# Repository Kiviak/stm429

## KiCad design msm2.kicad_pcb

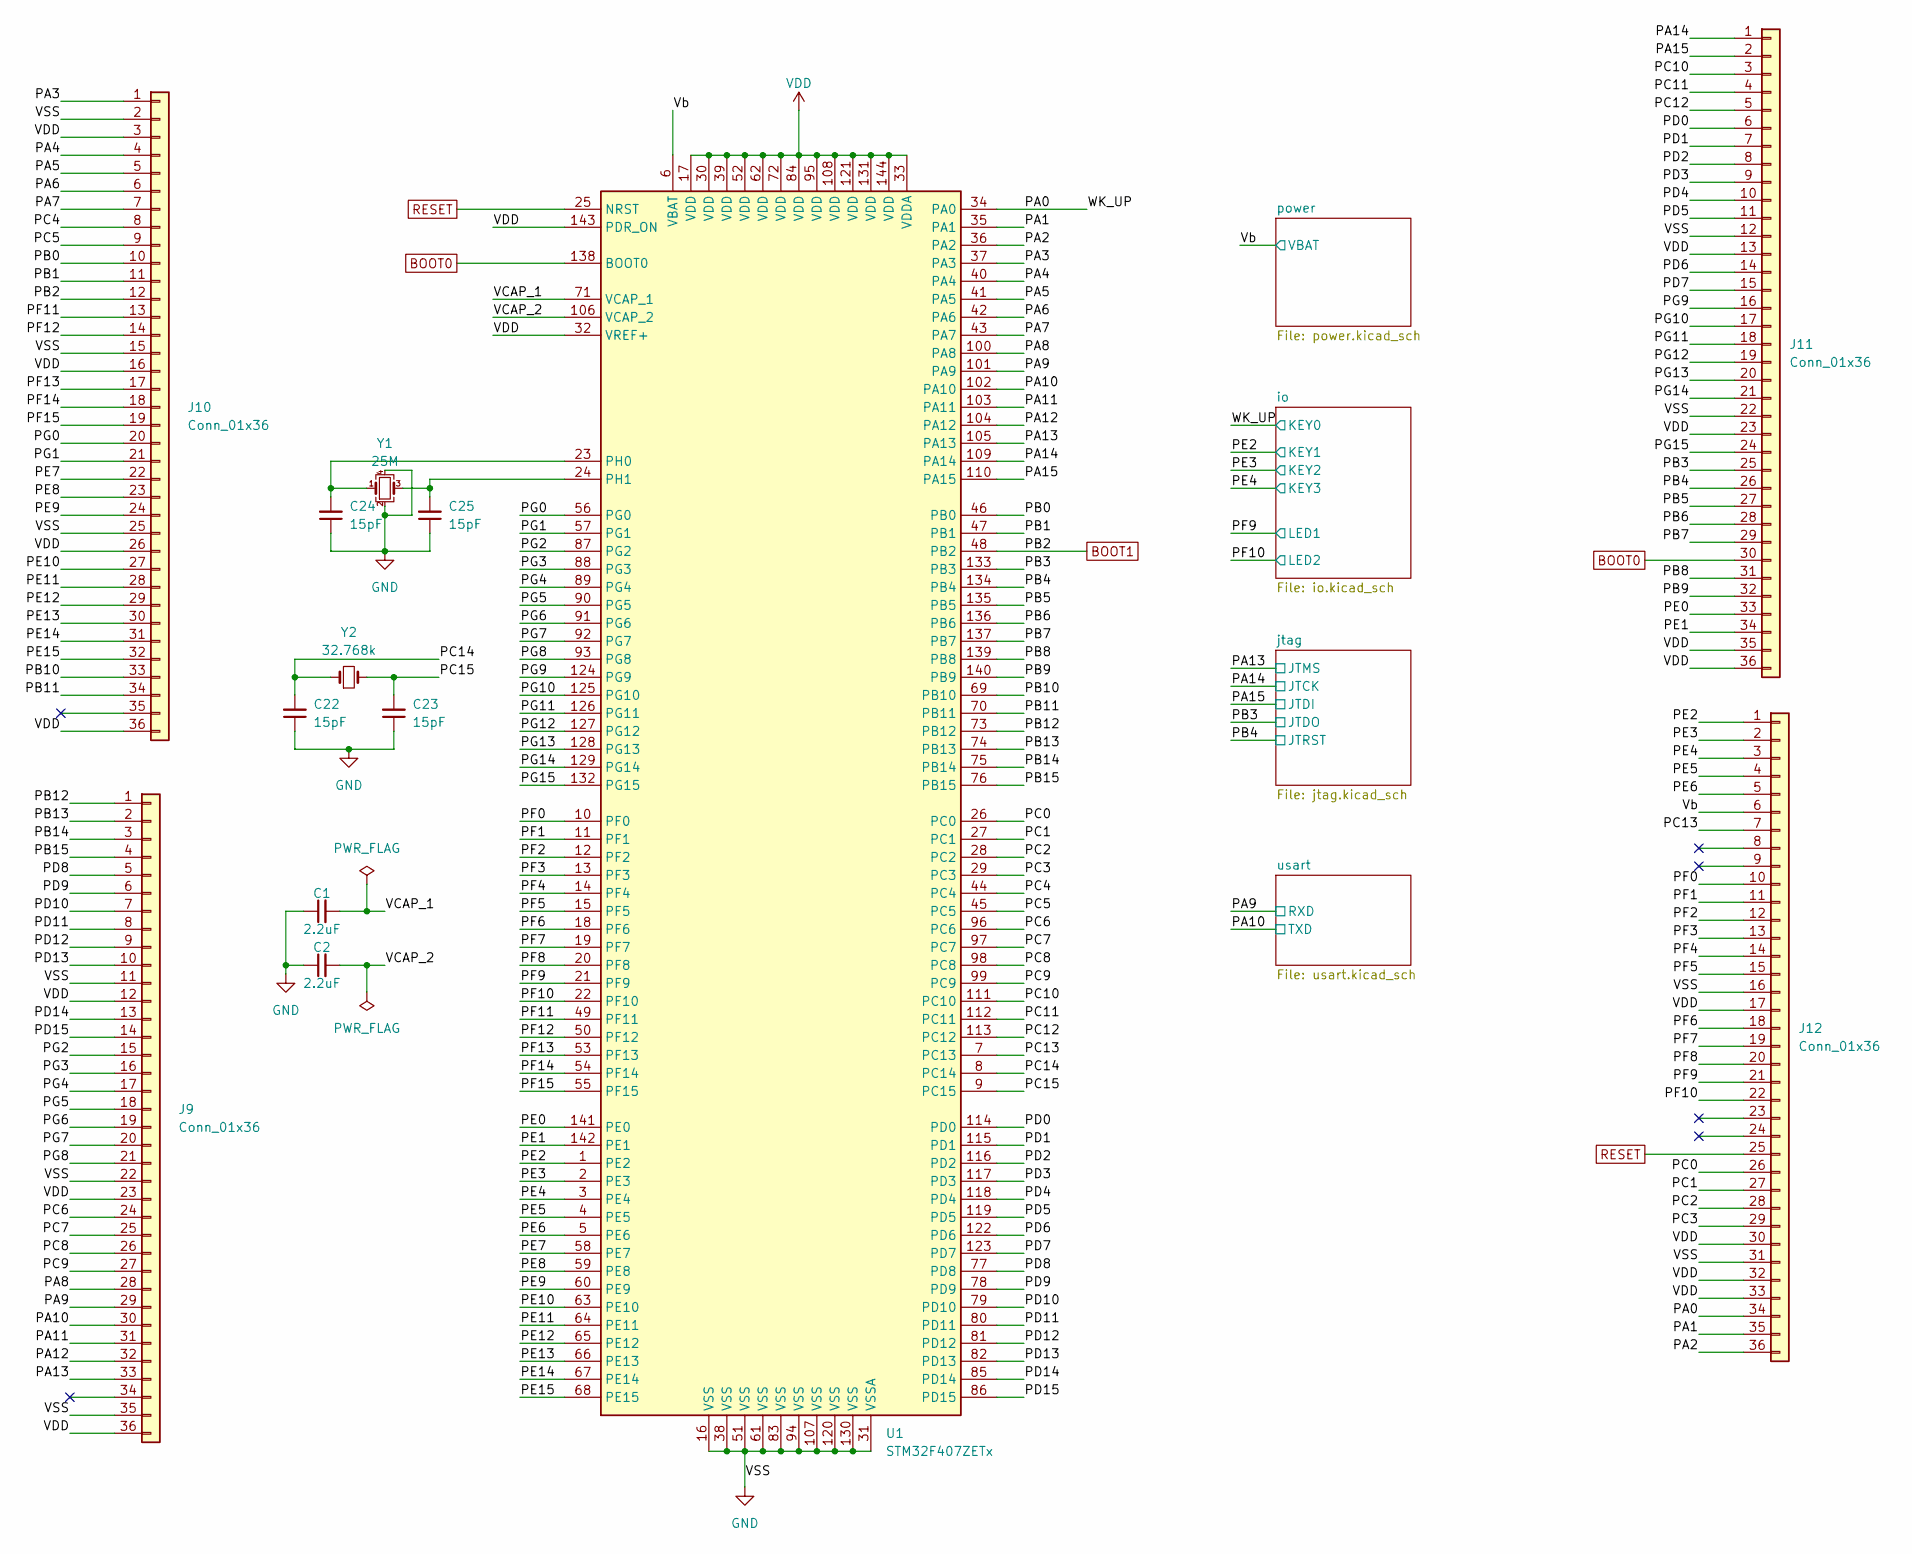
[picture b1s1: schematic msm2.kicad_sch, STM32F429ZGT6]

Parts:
C1, C2: 2.2uF; C_0603_1608Metric_Pad1.08x0.95mm_HandSolder
C22, C23, C24, C25: 15pF; C_0603_1608Metric_Pad1.08x0.95mm_HandSolder
J9, J10, J11, J12: Conn_01x36; PinHeader_1x36_P2.54mm_Vertical
U1: STM32F407ZETx; LQFP-144_20x20mm_P0.5mm
Y1: 25M; Crystal_SMD_3225-4Pin_3.2x2.5mm_HandSoldering
Y2: 32.768k; Crystal_SMD_3215-2Pin_3.2x1.5mm

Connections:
/PA0: J12.34, U1.34 (PA0); also elsewhere on the board
/PA1: J12.35, U1.35 (PA1)
/PA2: J12.36, U1.36 (PA2)
/PA3: J10.1, U1.37 (PA3)
/PA4: J10.4, U1.40 (PA4)
/PA5: J10.5, U1.41 (PA5)
/PA6: J10.6, U1.42 (PA6)
/PA7: J10.7, U1.43 (PA7)
/PA8: J9.28, U1.100 (PA8)
/PA9: J9.29, U1.101 (PA9); also elsewhere on the board
/PA10: J9.30, U1.102 (PA10); also elsewhere on the board
/PA11: J9.31, U1.103 (PA11)
/PA12: J9.32, U1.104 (PA12)
/PA13: J9.33, U1.105 (PA13); also elsewhere on the board
/PA14: J11.1, U1.109 (PA14); also elsewhere on the board
/PA15: J11.2, U1.110 (PA15); also elsewhere on the board
/PB0: J10.10, U1.46 (PB0)
/PB1: J10.11, U1.47 (PB1)
/PB3: J11.25, U1.133 (PB3); also elsewhere on the board
/PB4: J11.26, U1.134 (PB4); also elsewhere on the board
/PB5: J11.27, U1.135 (PB5)
/PB6: J11.28, U1.136 (PB6)
/PB7: J11.29, U1.137 (PB7)
/PB8: J11.31, U1.139 (PB8)
/PB9: J11.32, U1.140 (PB9)
/PB10: J10.33, U1.69 (PB10)
/PB11: J10.34, U1.70 (PB11)
/PB12: J9.1, U1.73 (PB12)
/PB13: J9.2, U1.74 (PB13)
/PB14: J9.3, U1.75 (PB14)
/PB15: J9.4, U1.76 (PB15)
/PC0: J12.26, U1.26 (PC0)
/PC1: J12.27, U1.27 (PC1)
/PC2: J12.28, U1.28 (PC2)
/PC3: J12.29, U1.29 (PC3)
/PC4: J10.8, U1.44 (PC4)
/PC5: J10.9, U1.45 (PC5)
/PC6: J9.24, U1.96 (PC6)
/PC7: J9.25, U1.97 (PC7)
/PC8: J9.26, U1.98 (PC8)
/PC9: J9.27, U1.99 (PC9)
/PC10: J11.3, U1.111 (PC10)
/PC11: J11.4, U1.112 (PC11)
/PC12: J11.5, U1.113 (PC12)
/PC13: J12.7, U1.7 (PC13)
/PC14: C22.2, U1.8 (PC14), Y2.1
/PC15: C23.2, U1.9 (PC15), Y2.2
/PD0: J11.6, U1.114 (PD0)
/PD1: J11.7, U1.115 (PD1)
/PD2: J11.8, U1.116 (PD2)
/PD3: J11.9, U1.117 (PD3)
/PD4: J11.10, U1.118 (PD4)
/PD5: J11.11, U1.119 (PD5)
/PD6: J11.14, U1.122 (PD6)
/PD7: J11.15, U1.123 (PD7)
/PD8: J9.5, U1.77 (PD8)
/PD9: J9.6, U1.78 (PD9)
/PD10: J9.7, U1.79 (PD10)
/PD11: J9.8, U1.80 (PD11)
/PD12: J9.9, U1.81 (PD12)
/PD13: J9.10, U1.82 (PD13)
/PD14: J9.13, U1.85 (PD14)
/PD15: J9.14, U1.86 (PD15)
/PE0: J11.33, U1.141 (PE0)
/PE1: J11.34, U1.142 (PE1)
/PE2: J12.1, U1.1 (PE2); also elsewhere on the board
/PE3: J12.2, U1.2 (PE3); also elsewhere on the board
/PE4: J12.3, U1.3 (PE4); also elsewhere on the board
/PE5: J12.4, U1.4 (PE5)
/PE6: J12.5, U1.5 (PE6)
/PE7: J10.22, U1.58 (PE7)
/PE8: J10.23, U1.59 (PE8)
/PE9: J10.24, U1.60 (PE9)
/PE10: J10.27, U1.63 (PE10)
/PE11: J10.28, U1.64 (PE11)
/PE12: J10.29, U1.65 (PE12)
/PE13: J10.30, U1.66 (PE13)
/PE14: J10.31, U1.67 (PE14)
/PE15: J10.32, U1.68 (PE15)
/PF0: J12.10, U1.10 (PF0)
/PF1: J12.11, U1.11 (PF1)
/PF2: J12.12, U1.12 (PF2)
/PF3: J12.13, U1.13 (PF3)
/PF4: J12.14, U1.14 (PF4)
/PF5: J12.15, U1.15 (PF5)
/PF6: J12.18, U1.18 (PF6)
/PF7: J12.19, U1.19 (PF7)
/PF8: J12.20, U1.20 (PF8)
/PF9: J12.21, U1.21 (PF9); also elsewhere on the board
/PF10: J12.22, U1.22 (PF10); also elsewhere on the board
/PF11: J10.13, U1.49 (PF11)
/PF12: J10.14, U1.50 (PF12)
/PF13: J10.17, U1.53 (PF13)
/PF14: J10.18, U1.54 (PF14)
/PF15: J10.19, U1.55 (PF15)
/PG0: J10.20, U1.56 (PG0)
/PG1: J10.21, U1.57 (PG1)
/PG2: J9.15, U1.87 (PG2)
/PG3: J9.16, U1.88 (PG3)
/PG4: J9.17, U1.89 (PG4)
/PG5: J9.18, U1.90 (PG5)
/PG6: J9.19, U1.91 (PG6)
/PG7: J9.20, U1.92 (PG7)
/PG8: J9.21, U1.93 (PG8)
/PG9: J11.16, U1.124 (PG9)
/PG10: J11.17, U1.125 (PG10)
/PG11: J11.18, U1.126 (PG11)
/PG12: J11.19, U1.127 (PG12)
/PG13: J11.20, U1.128 (PG13)
/PG14: J11.21, U1.129 (PG14)
/PG15: J11.24, U1.132 (PG15)
/VCAP_1: C1.2, U1.71 (VCAP_1)
/VCAP_2: C2.2, U1.106 (VCAP_2)
/Vb: J12.6, U1.6 (VBAT); also elsewhere on the board
BOOT0: J11.30, U1.138 (BOOT0); also elsewhere on the board
BOOT1: J10.12, U1.48 (PB2); also elsewhere on the board
GND: C1.1, C2.1, C22.1, C23.1, C24.1, C25.1, J9.11, J9.22, J9.35, J10.2, J10.15, J10.25, J11.12, J11.22, J12.16, J12.31, U1.16 (VSS), U1.31 (VSSA), U1.38 (VSS), U1.51 (VSS), U1.61 (VSS), U1.83 (VSS), U1.94 (VSS), U1.107 (VSS), U1.120 (VSS), U1.130 (VSS), Y1.2, Y1.4; also elsewhere on the board
unnamed: C24.2, U1.23 (PH0), Y1.1
unnamed: C25.2, U1.24 (PH1), Y1.3
RESET: J12.25, U1.25 (NRST); also elsewhere on the board
VDD: J9.12, J9.23, J9.36, J10.3, J10.16, J10.26, J10.36, J11.13, J11.23, J11.35, J11.36, J12.17, J12.30, J12.32, J12.33, U1.17 (VDD), U1.30 (VDD), U1.32 (VREF+), U1.33 (VDDA), U1.39 (VDD), U1.52 (VDD), U1.62 (VDD), U1.72 (VDD), U1.84 (VDD), U1.95 (VDD), U1.108 (VDD), U1.121 (VDD), U1.131 (VDD), U1.143 (PDR_ON), U1.144 (VDD); also elsewhere on the board

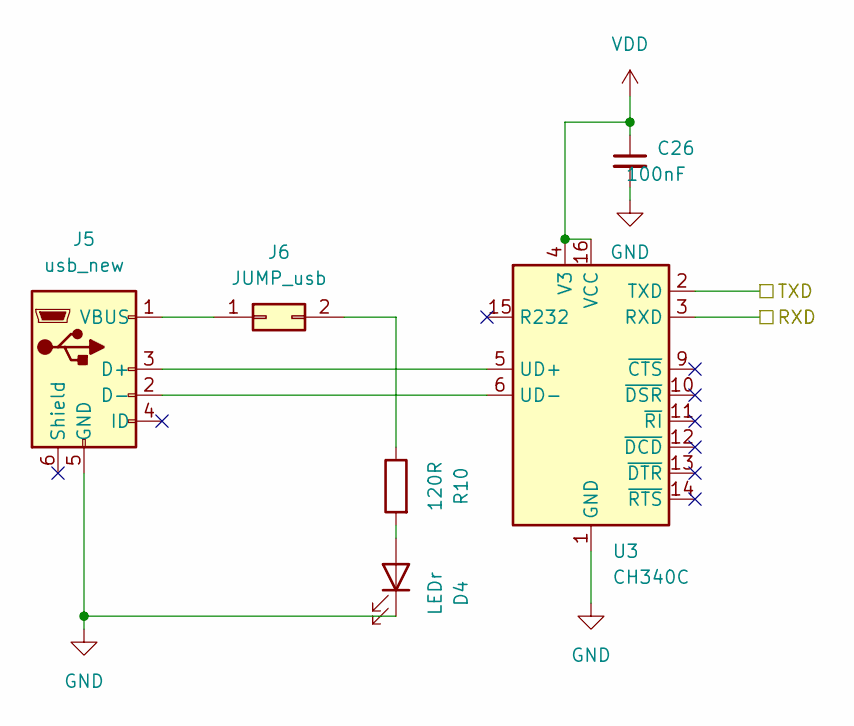
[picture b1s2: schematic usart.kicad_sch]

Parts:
C26: 100nF; C_0603_1608Metric_Pad1.08x0.95mm_HandSolder
D4: LEDr; LED_0603_1608Metric_Pad1.05x0.95mm_HandSolder
J5: usb_new; USB_Micro-B_GCT_USB3076-30-A
J6: JUMP_usb; PinHeader_2x01_P2.54mm_Vertical
R10: 120R; R_0603_1608Metric_Pad0.98x0.95mm_HandSolder
U3: CH340C; SOIC-16_3.9x9.9mm_P1.27mm

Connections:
/PA9: U3.3 (RXD); also elsewhere on the board
/PA10: U3.2 (TXD); also elsewhere on the board
GND: C26.2, D4.1 (K), J5.5 (GND), U3.1 (GND); also elsewhere on the board
unnamed: D4.2 (A), R10.2
unnamed: J5.1 (VBUS), J6.1
unnamed: J5.2 (D-), U3.6 (UD-)
unnamed: J5.3 (D+), U3.5 (UD+)
unnamed: J6.2, R10.1
VDD: C26.1, U3.4 (V3), U3.16 (VCC); also elsewhere on the board

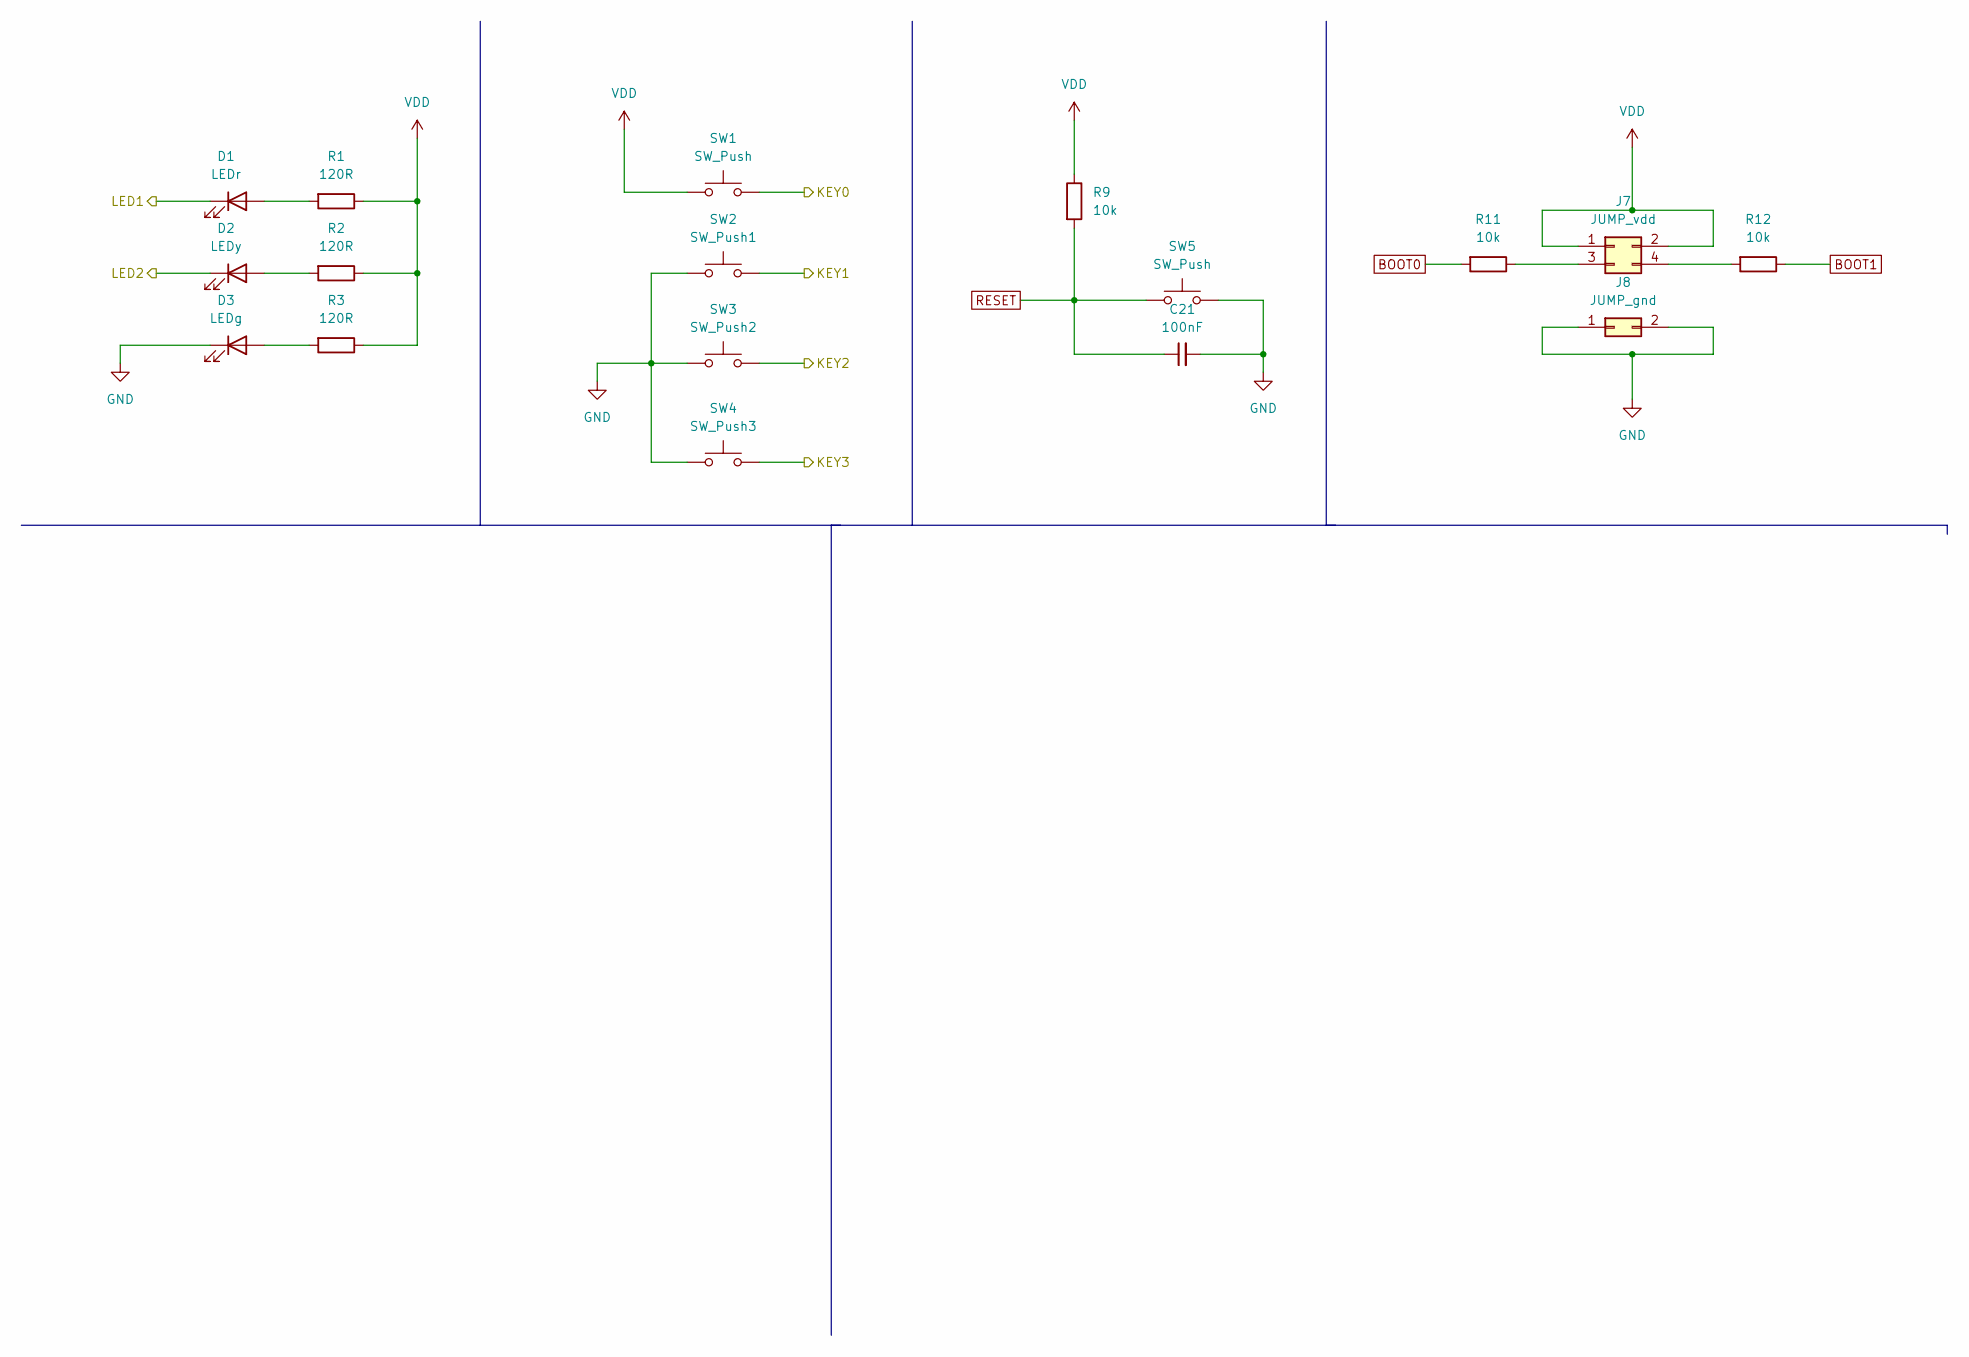
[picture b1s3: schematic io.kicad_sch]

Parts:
C21: 100nF; C_0603_1608Metric_Pad1.08x0.95mm_HandSolder
D1: LEDr; LED_0603_1608Metric_Pad1.05x0.95mm_HandSolder
D2: LEDy; LED_0603_1608Metric_Pad1.05x0.95mm_HandSolder
D3: LEDg; LED_0603_1608Metric_Pad1.05x0.95mm_HandSolder
J7: JUMP_vdd; PinHeader_2x02_P2.54mm_Vertical
J8: JUMP_gnd; PinHeader_2x01_P2.54mm_Vertical
R1, R2, R3: 120R; R_0603_1608Metric_Pad0.98x0.95mm_HandSolder
R9, R11, R12: 10k; R_0603_1608Metric_Pad0.98x0.95mm_HandSolder
SW1, SW5: SW_Push; SW_Push_6x3.6mm_H2.5mm
SW2: SW_Push1; SW_Push_6x3.6mm_H2.5mm
SW3: SW_Push2; SW_Push_6x3.6mm_H2.5mm
SW4: SW_Push3; SW_Push_6x3.6mm_H2.5mm

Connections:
/PA0: SW1.2; also elsewhere on the board
/PE2: SW2.2; also elsewhere on the board
/PE3: SW3.2; also elsewhere on the board
/PE4: SW4.2; also elsewhere on the board
/PF9: D1.1 (K); also elsewhere on the board
/PF10: D2.1 (K); also elsewhere on the board
BOOT0: R11.2; also elsewhere on the board
BOOT1: R12.1; also elsewhere on the board
GND: C21.2, D3.1 (K), J8.1, J8.2, SW2.1, SW3.1, SW4.1, SW5.2; also elsewhere on the board
unnamed: D1.2 (A), R1.2
unnamed: D2.2 (A), R2.2
unnamed: D3.2 (A), R3.2
unnamed: J7.3, R11.1
unnamed: J7.4, R12.2
RESET: C21.1, R9.2, SW5.1; also elsewhere on the board
VDD: J7.1, J7.2, R1.1, R2.1, R3.1, R9.1, SW1.1; also elsewhere on the board

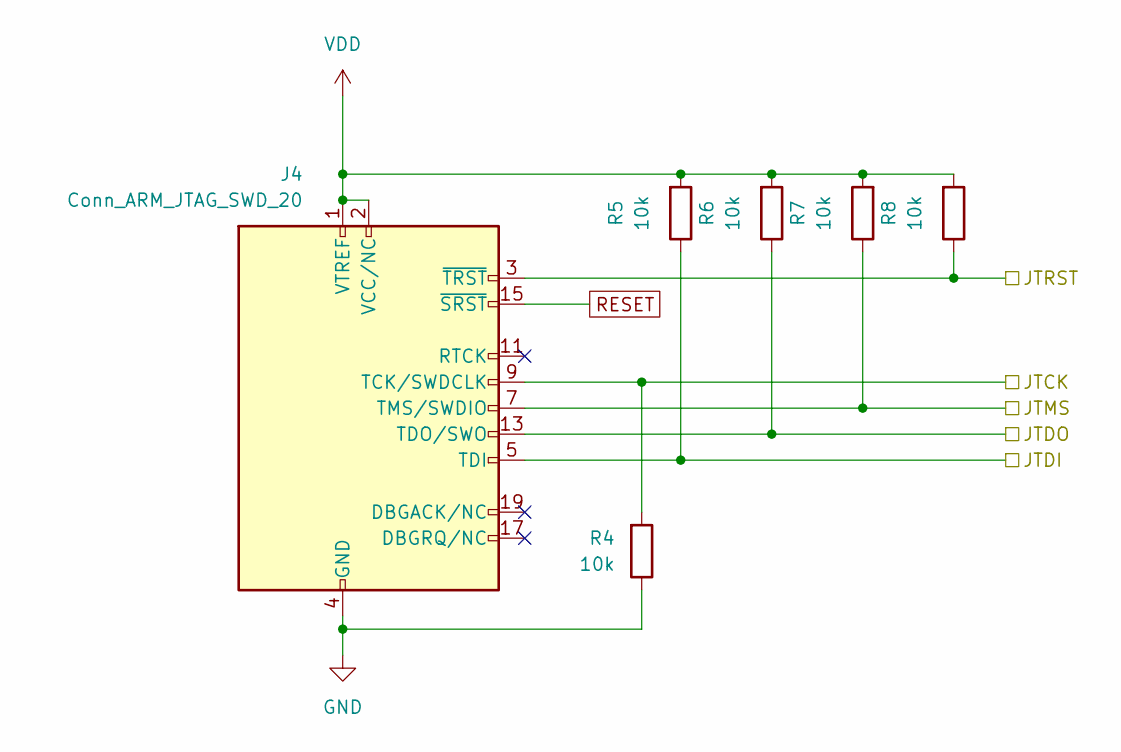
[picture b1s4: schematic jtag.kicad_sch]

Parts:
J4: Conn_ARM_JTAG_SWD_20; IDC-Header_2x10_P2.54mm_Vertical
R4, R5, R6, R7, R8: 10k; R_0603_1608Metric_Pad0.98x0.95mm_HandSolder

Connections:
/PA13: J4.7 (TMS/SWDIO), R7.1; also elsewhere on the board
/PA14: J4.9 (TCK/SWDCLK), R4.2; also elsewhere on the board
/PA15: J4.5 (TDI), R5.1; also elsewhere on the board
/PB3: J4.13 (TDO/SWO), R6.1; also elsewhere on the board
/PB4: J4.3 (~TRST), R8.1; also elsewhere on the board
GND: J4.4 (GND), J4.6 (GND), J4.8 (GND), J4.10 (GND), J4.12 (GND), J4.14 (GND), J4.16 (GND), J4.18 (GND), J4.20 (GND), R4.1; also elsewhere on the board
RESET: J4.15 (~SRST); also elsewhere on the board
VDD: J4.1 (VTREF), J4.2 (VCC/NC), R5.2, R6.2, R7.2, R8.2; also elsewhere on the board

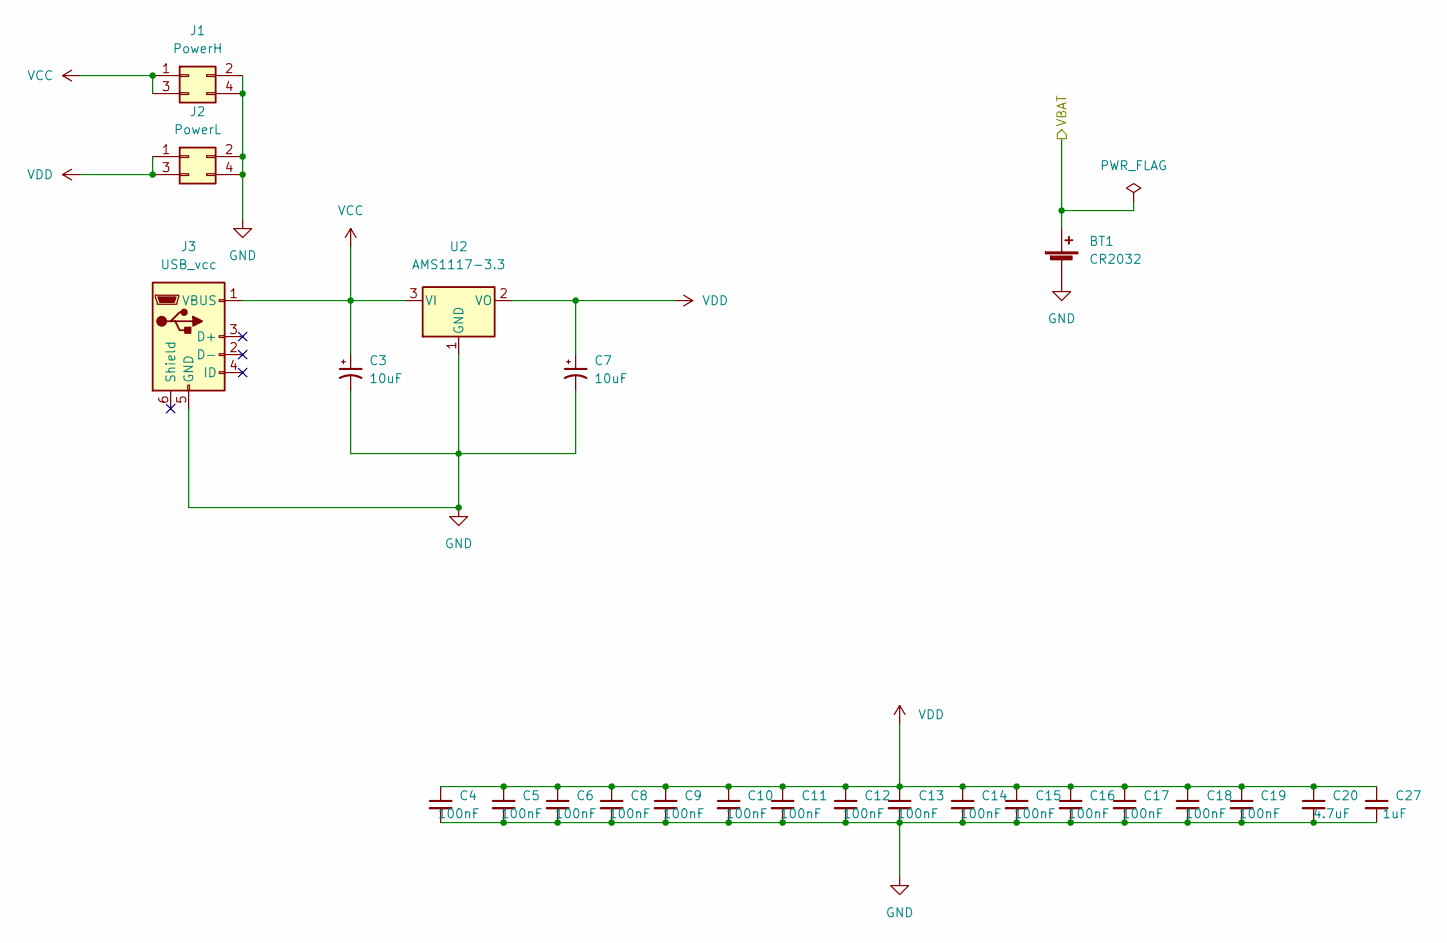
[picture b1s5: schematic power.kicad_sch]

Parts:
BT1: CR2032; BatteryHolder_Keystone_3002_1x2032
C3, C7: 10uF; CP_EIA-3528-15_AVX-H_Pad1.50x2.35mm_HandSolder
C4, C5, C6, C8, C9, C10, C11, C12, C13, C14, C15, C16, C17, C18, C19: 100nF; C_0603_1608Metric_Pad1.08x0.95mm_HandSolder
C20: 4.7uF; C_0805_2012Metric_Pad1.18x1.45mm_HandSolder
C27: 1uF; C_0603_1608Metric_Pad1.08x0.95mm_HandSolder
J1: PowerH; PinHeader_2x02_P2.54mm_Vertical
J2: PowerL; PinHeader_2x02_P2.54mm_Vertical
J3: USB_vcc; USB_Micro-B_GCT_USB3076-30-A
U2: AMS1117-3.3; SOT-223-3_TabPin2

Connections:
/Vb: BT1.1 (+); also elsewhere on the board
GND: BT1.2 (-), C3.2, C4.2, C5.2, C6.2, C7.2, C8.2, C9.2, C10.2, C11.2, C12.2, C13.2, C14.2, C15.2, C16.2, C17.2, C18.2, C19.2, C20.2, C27.2, J1.2, J1.4, J2.2, J2.4, J3.5 (GND), U2.1 (GND); also elsewhere on the board
VCC: C3.1, J1.1, J1.3, J3.1 (VBUS), U2.3 (VI)
VDD: C4.1, C5.1, C6.1, C7.1, C8.1, C9.1, C10.1, C11.1, C12.1, C13.1, C14.1, C15.1, C16.1, C17.1, C18.1, C19.1, C20.1, C27.1, J2.1, J2.3, U2.2 (VO); also elsewhere on the board

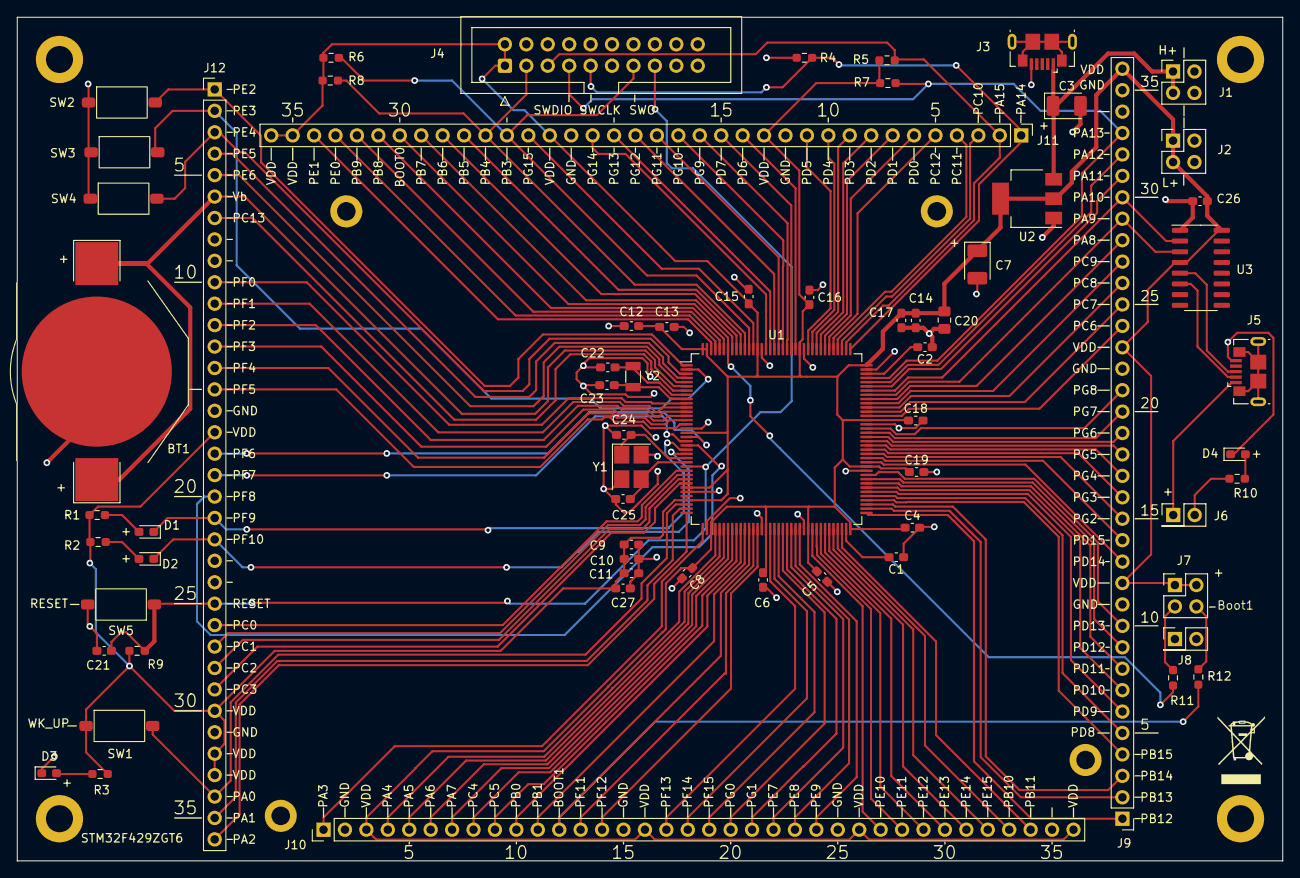
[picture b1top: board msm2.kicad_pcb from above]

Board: 2 copper layers, 150.0 x 100.0 mm, 66 parts (0 on the bottom side), 132 nets.

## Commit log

2022-09-11 init
2022-09-12 v1.0
2022-09-12 good pcb
2022-09-14 pcb v2.0
2022-09-14 pcb v3.0
2022-09-15 pcb v3.1
2022-09-15 v3.1 all
2022-09-15 v3.2
2022-09-18 v3.3
2022-09-18 v3.4
2022-09-21 v3.5
2022-09-26 v3.6
